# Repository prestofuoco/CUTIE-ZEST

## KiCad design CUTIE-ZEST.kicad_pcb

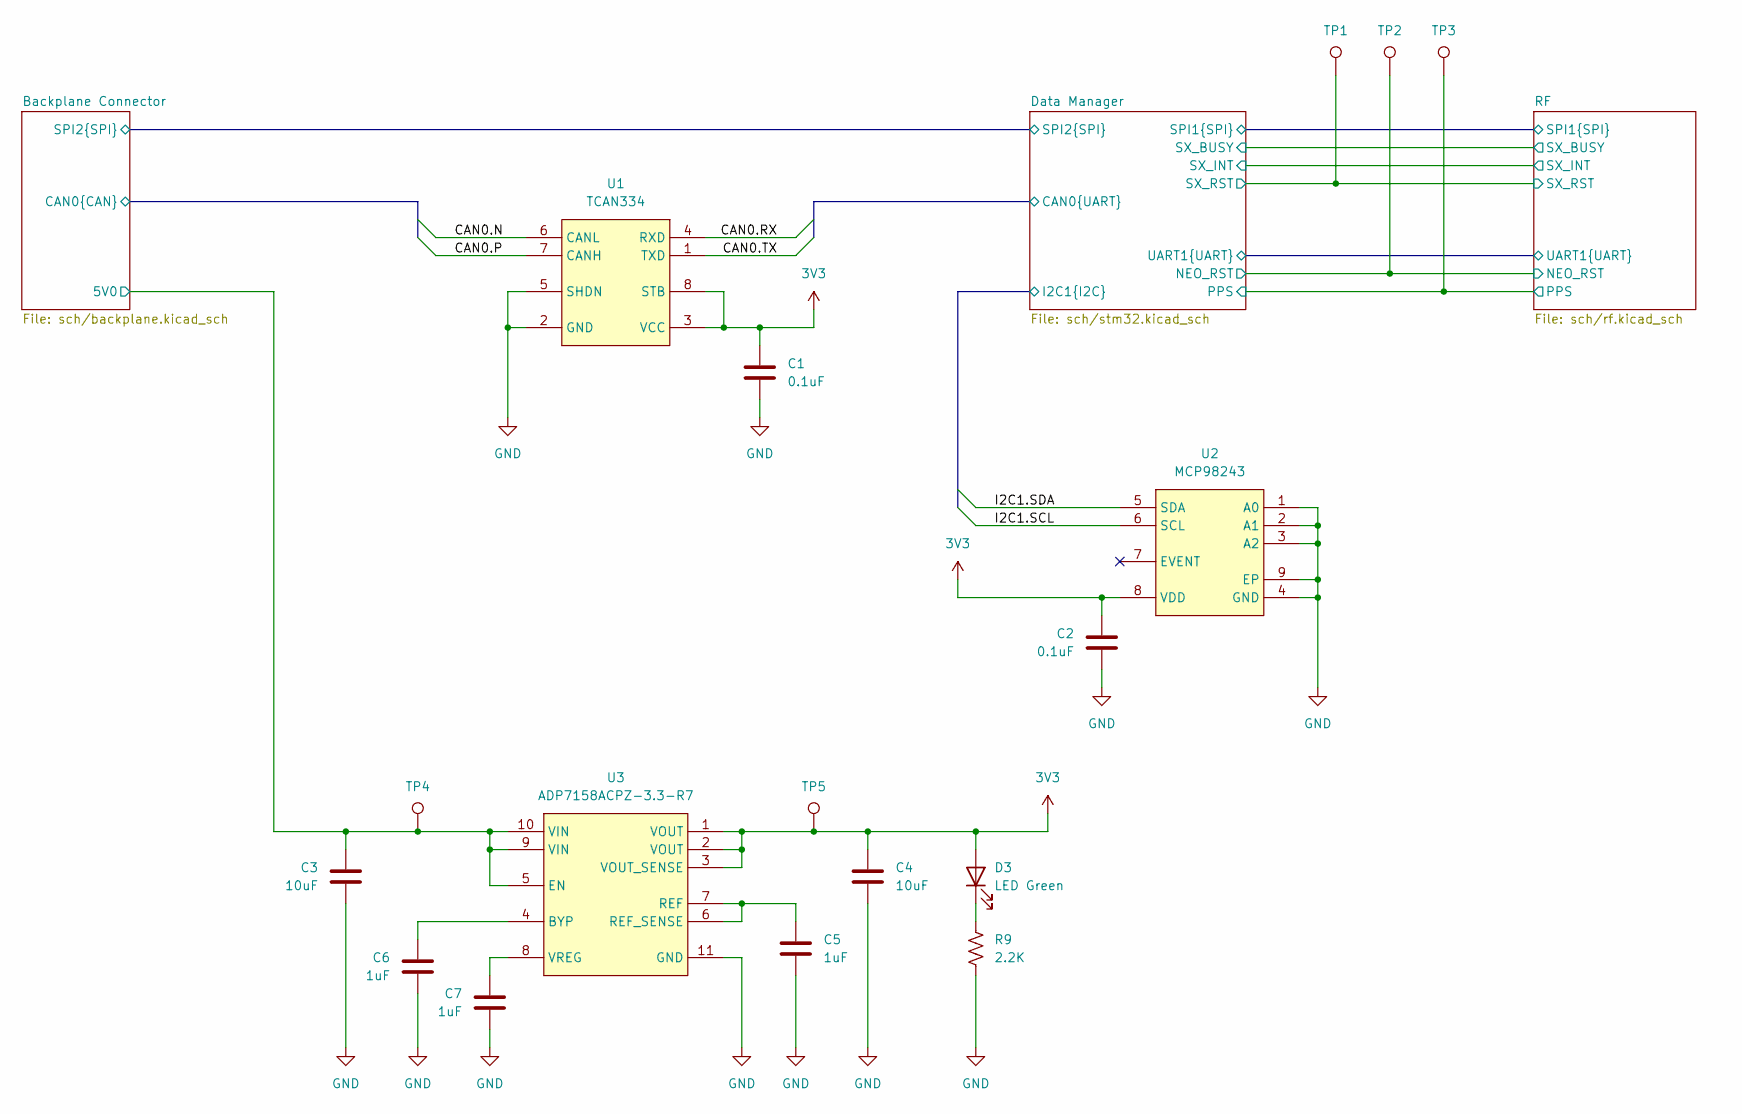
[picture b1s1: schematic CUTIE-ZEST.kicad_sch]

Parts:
C1, C2: 0.1uF; C_0402_1005Metric
C3, C4: 10uF; C_0603_1608Metric
C5, C6, C7: 1uF; C_0603_1608Metric
D3: LED Green; LED_0805_2012Metric
R9: 2.2K; R_0402_1005Metric
TP1, TP2, TP3, TP4, TP5: TestPoint; TestPoint_Pad_D1.0mm
U1: TCAN334; JEITA_SOIC-8_3.9x4.9mm_P1.27mm
U2: MCP98243; DFN-8-1EP_3x2mm_P0.5mm_EP1.3x1.5mm
U3: ADP7158ACPZ-3.3-R7; CP-10-9_ADI

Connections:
3V3: C1.1, C2.1, C4.1, D3.2 (A), TP5.1 (1_1), U1.3 (VCC), U1.8 (STB), U2.8 (VDD), U3.1 (VOUT), U3.2 (VOUT), U3.3 (VOUT_SENSE); also elsewhere on the board
/Backplane Connector/5V0: C3.1, TP4.1 (1_1), U3.5 (EN), U3.9 (VIN), U3.10 (VIN); also elsewhere on the board
/Backplane Connector/CAN0.N: U1.6 (CANL); also elsewhere on the board
/Backplane Connector/CAN0.P: U1.7 (CANH); also elsewhere on the board
/Data Manager/CAN0.RX: U1.4 (RXD); also elsewhere on the board
/Data Manager/CAN0.TX: U1.1 (TXD); also elsewhere on the board
/Data Manager/I2C1.SCL: U2.6 (SCL); also elsewhere on the board
/Data Manager/I2C1.SDA: U2.5 (SDA); also elsewhere on the board
/Data Manager/NEO_RST: TP2.1 (1_1); also elsewhere on the board
/Data Manager/PPS: TP3.1 (1_1); also elsewhere on the board
/Data Manager/SX_RST: TP1.1 (1_1); also elsewhere on the board
GND: C1.2, C2.2, C3.2, C4.2, C5.2, C6.2, C7.2, R9.2, U1.2 (GND), U1.5 (SHDN), U2.1 (A0), U2.2 (A1), U2.3 (A2), U2.4 (GND), U2.9 (EP), U3.11 (GND); also elsewhere on the board
unnamed: D3.1 (K), R9.1
unnamed: C6.1, U3.4 (BYP)
unnamed: C5.1, U3.6 (REF_SENSE), U3.7 (REF)
unnamed: C7.1, U3.8 (VREG)

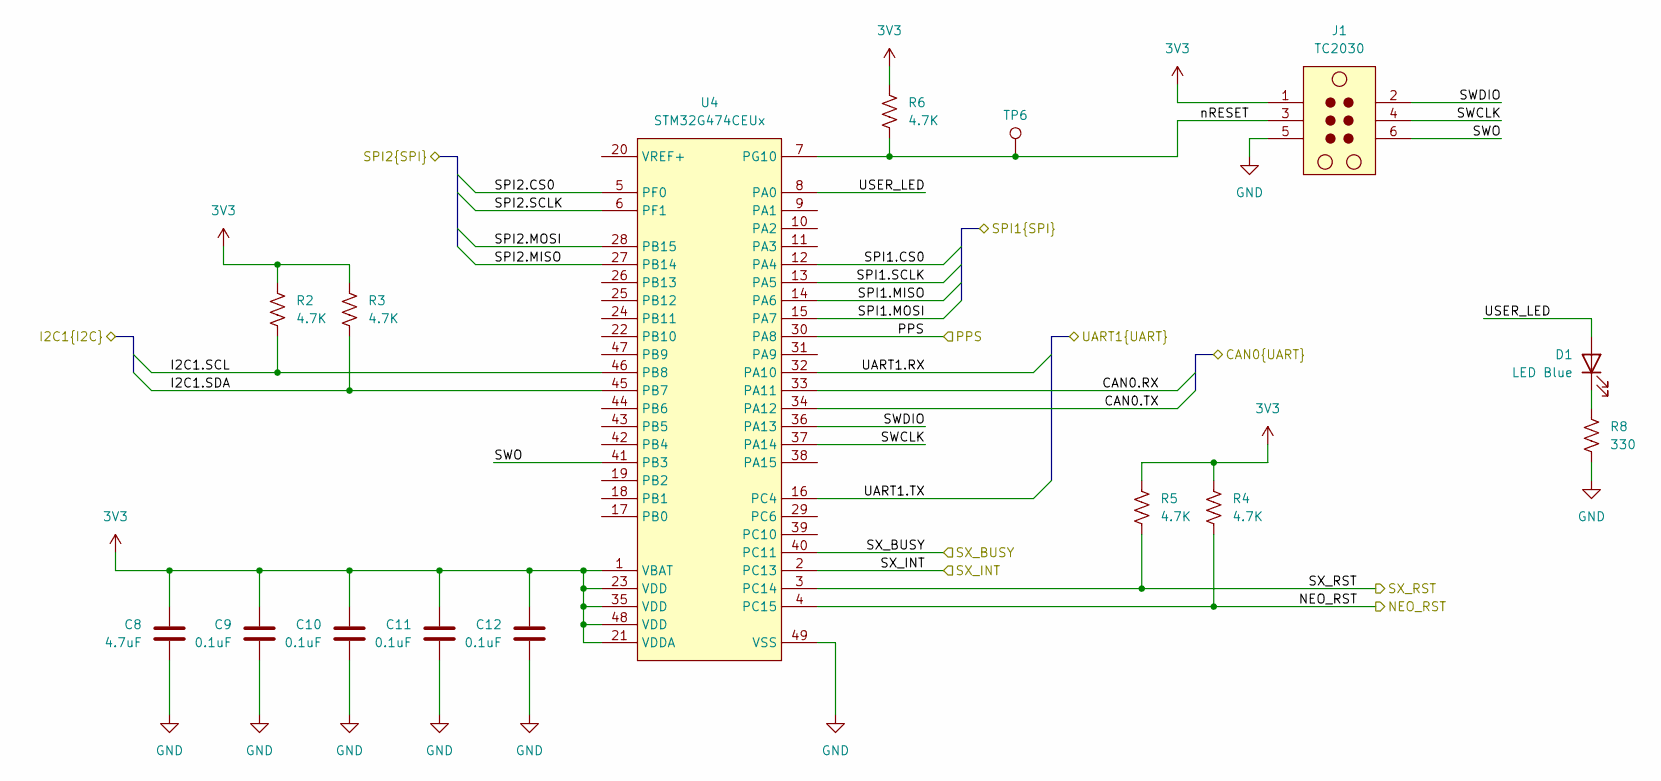
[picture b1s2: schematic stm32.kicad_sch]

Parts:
C8: 4.7uF; C_0603_1608Metric
C9, C10, C11, C12: 0.1uF; C_0402_1005Metric
D1: LED Blue; LED_0805_2012Metric
J1: TC2030; Tag-Connect_TC2030-IDC-NL_2x03_P1.27mm_Vertical
R2, R3, R4, R5, R6: 4.7K; R_0402_1005Metric
R8: 330; R_0402_1005Metric
TP6: TestPoint; TestPoint_Pad_D1.0mm
U4: STM32G474CEUx; QFN-48-1EP_7x7mm_P0.5mm_EP5.6x5.6mm

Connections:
3V3: C8.1, C9.1, C10.1, C11.1, C12.1, J1.1, R2.1, R3.1, R4.1, R5.1, R6.1, U4.1 (VBAT), U4.21 (VDDA), U4.23 (VDD), U4.35 (VDD), U4.48 (VDD); also elsewhere on the board
/Backplane Connector/SPI2.CS0: U4.5 (PF0); also elsewhere on the board
/Backplane Connector/SPI2.MISO: U4.27 (PB14); also elsewhere on the board
/Backplane Connector/SPI2.MOSI: U4.28 (PB15); also elsewhere on the board
/Backplane Connector/SPI2.SCLK: U4.6 (PF1); also elsewhere on the board
/Data Manager/CAN0.RX: U4.33 (PA11); also elsewhere on the board
/Data Manager/CAN0.TX: U4.34 (PA12); also elsewhere on the board
/Data Manager/I2C1.SCL: R2.2, U4.46 (PB8); also elsewhere on the board
/Data Manager/I2C1.SDA: R3.2, U4.45 (PB7); also elsewhere on the board
/Data Manager/NEO_RST: R4.2, U4.4 (PC15); also elsewhere on the board
/Data Manager/PPS: U4.30 (PA8); also elsewhere on the board
/Data Manager/SPI1.CS0: U4.12 (PA4); also elsewhere on the board
/Data Manager/SPI1.MISO: U4.14 (PA6); also elsewhere on the board
/Data Manager/SPI1.MOSI: U4.15 (PA7); also elsewhere on the board
/Data Manager/SPI1.SCLK: U4.13 (PA5); also elsewhere on the board
/Data Manager/SWCLK: J1.4, U4.37 (PA14)
/Data Manager/SWDIO: J1.2, U4.36 (PA13)
/Data Manager/SWO: J1.6, U4.41 (PB3)
/Data Manager/SX_BUSY: U4.40 (PC11); also elsewhere on the board
/Data Manager/SX_INT: U4.2 (PC13); also elsewhere on the board
/Data Manager/SX_RST: R5.2, U4.3 (PC14); also elsewhere on the board
/Data Manager/UART1.RX: U4.32 (PA10); also elsewhere on the board
/Data Manager/UART1.TX: U4.16 (PC4); also elsewhere on the board
/Data Manager/USER_LED: D1.2 (A), U4.8 (PA0)
/Data Manager/nRESET: J1.3, R6.2, TP6.1 (1_1), U4.7 (PG10)
GND: C8.2, C9.2, C10.2, C11.2, C12.2, J1.5, R8.2, U4.49 (VSS); also elsewhere on the board
unnamed: D1.1 (K), R8.1

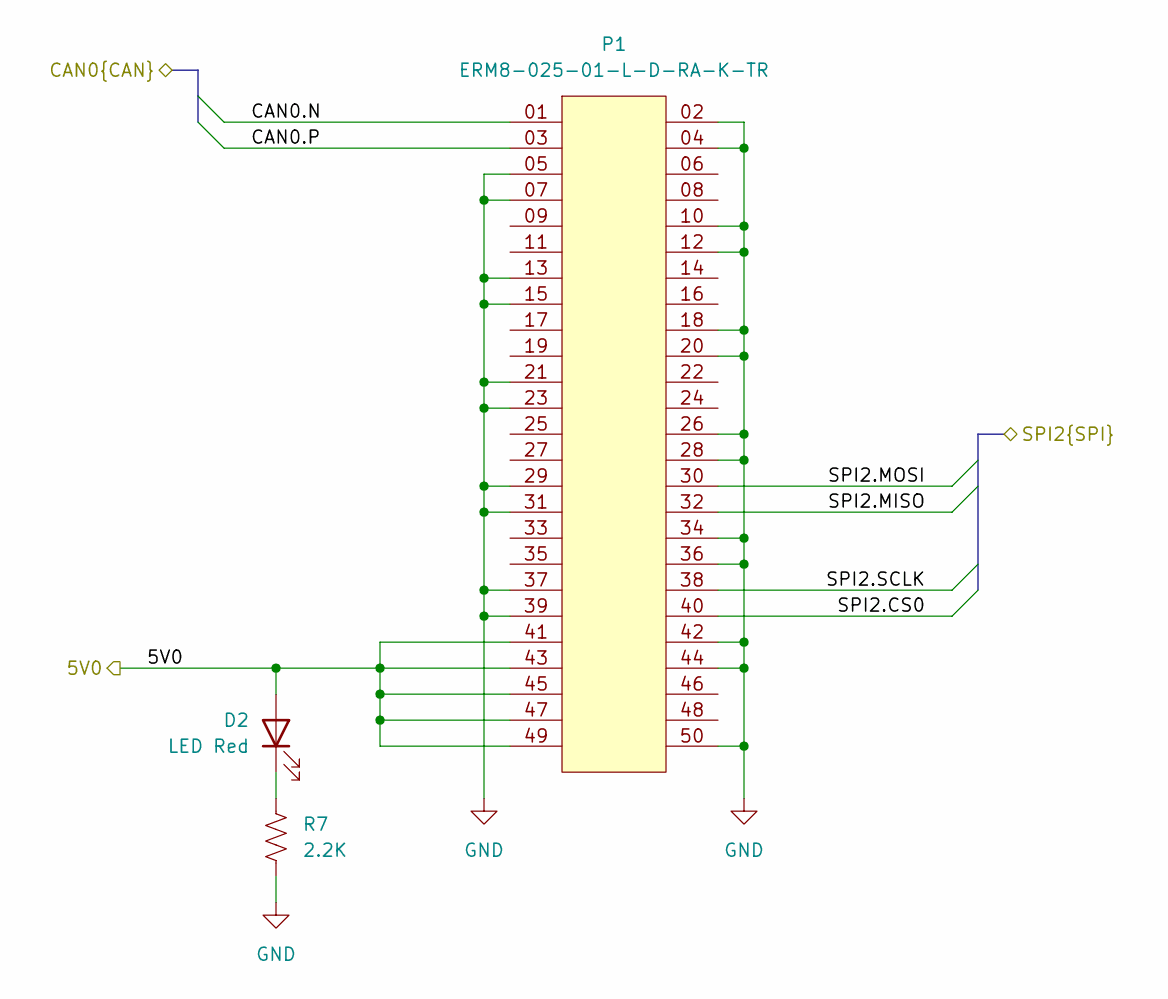
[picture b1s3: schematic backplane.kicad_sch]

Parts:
D2: LED Red; LED_0805_2012Metric
P1: ERM8-025-01-L-D-RA-K-TR; SAMTEC_ERM8-025-XX-X-D-RA-XX
R7: 2.2K; R_0402_1005Metric

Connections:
/Backplane Connector/5V0: D2.2 (A), P1.41, P1.43, P1.45, P1.47, P1.49; also elsewhere on the board
/Backplane Connector/CAN0.N: P1.01; also elsewhere on the board
/Backplane Connector/CAN0.P: P1.03; also elsewhere on the board
/Backplane Connector/SPI2.CS0: P1.40; also elsewhere on the board
/Backplane Connector/SPI2.MISO: P1.32; also elsewhere on the board
/Backplane Connector/SPI2.MOSI: P1.30; also elsewhere on the board
/Backplane Connector/SPI2.SCLK: P1.38; also elsewhere on the board
GND: P1.02, P1.04, P1.05, P1.07, P1.10, P1.12, P1.13, P1.15, P1.18, P1.20, P1.21, P1.23, P1.26, P1.28, P1.29, P1.31, P1.34, P1.36, P1.37, P1.39, P1.42, P1.44, P1.50, R7.2; also elsewhere on the board
unnamed: D2.1 (K), R7.1

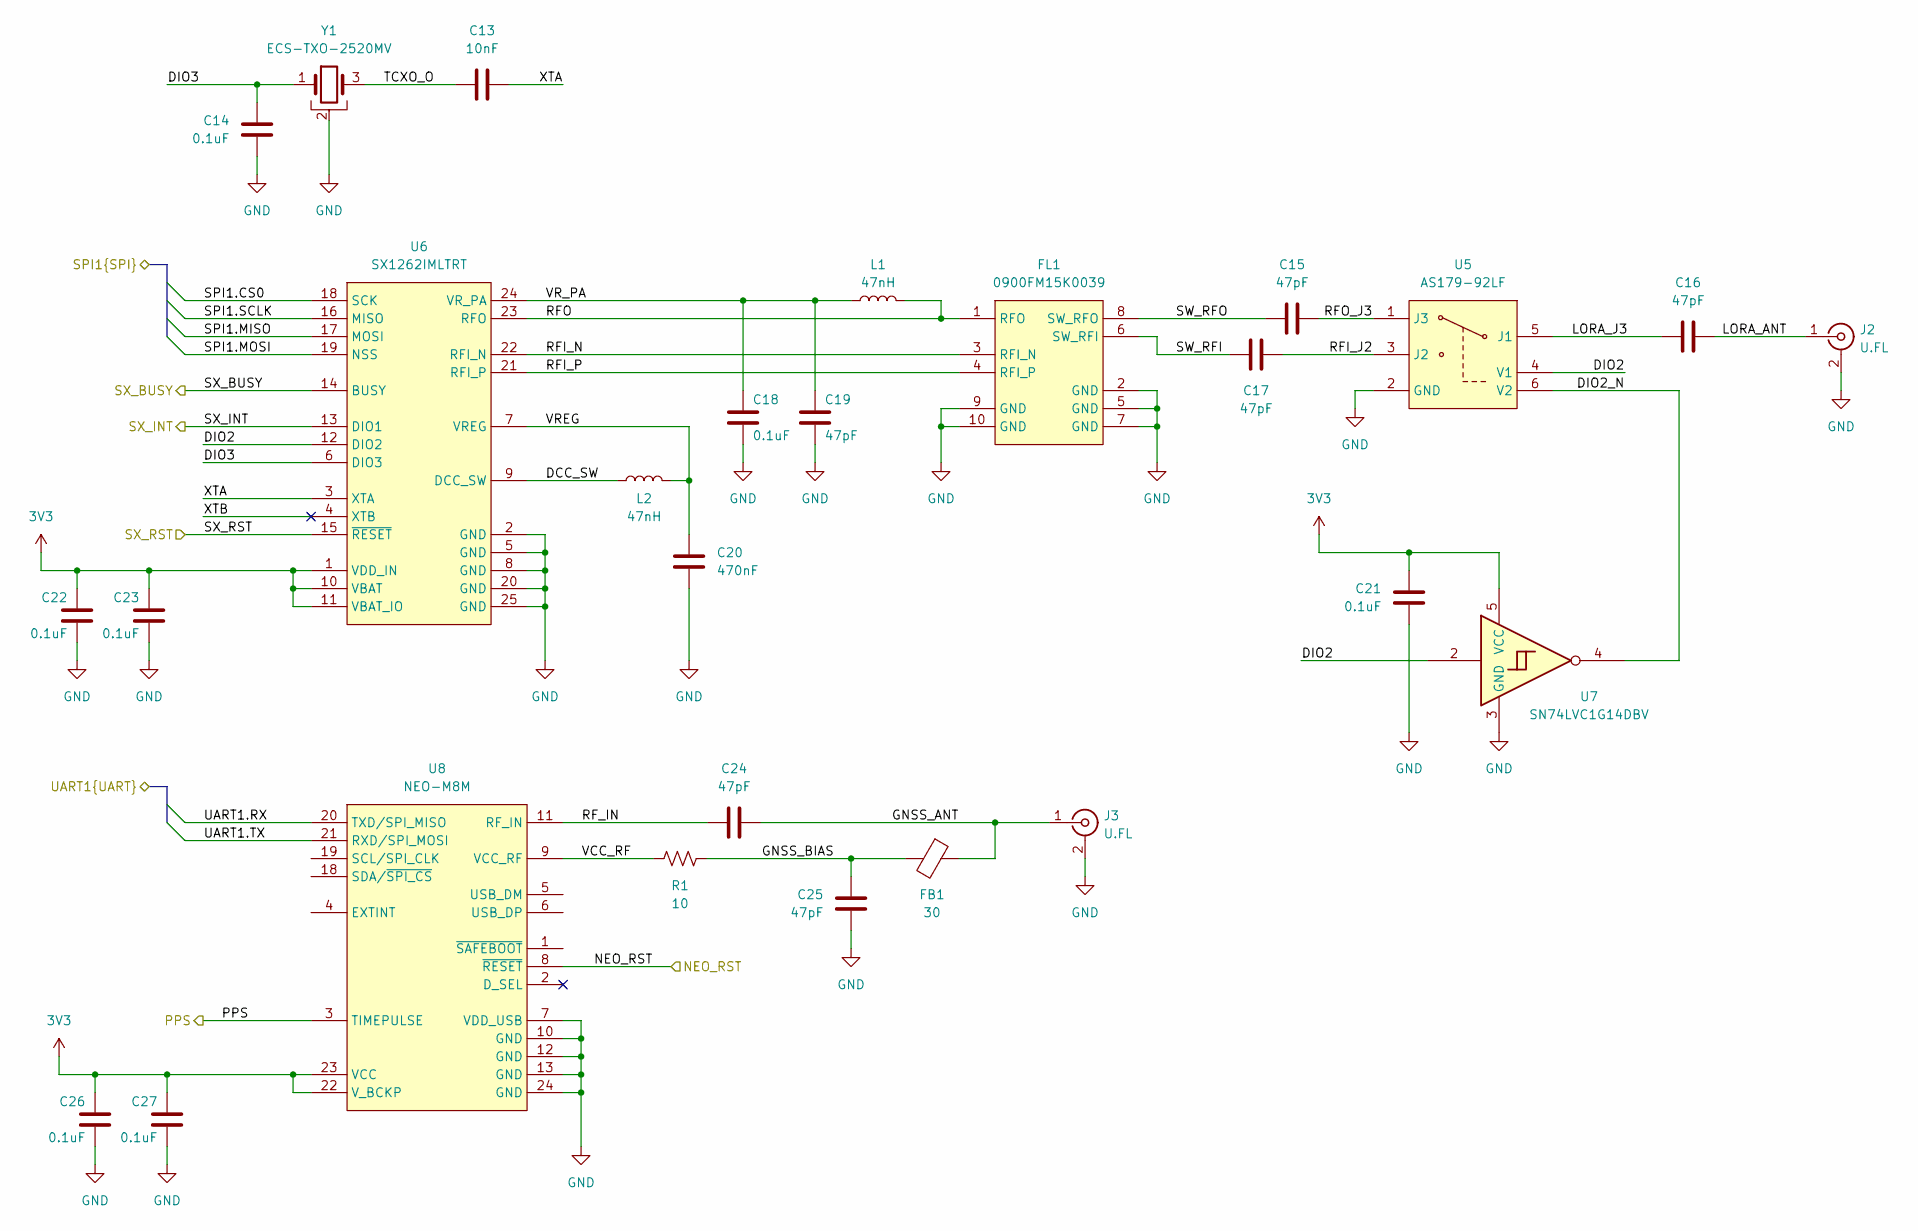
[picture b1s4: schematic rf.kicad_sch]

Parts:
C13: 10nF; C_0402_1005Metric
C14, C18, C21, C22, C23, C26, C27: 0.1uF; C_0402_1005Metric
C15, C16, C17, C19, C24, C25: 47pF; C_0402_1005Metric
C20: 470nF; C_0402_1005Metric
FB1: 30; L_0805_2012Metric
FL1: 0900FM15K0039; Balun_Johanson_0900FM15K0039
J2, J3: U.FL; U.FL_Hirose_U.FL-R-SMT-1_Vertical
L1, L2: 47nH; L_0402_1005Metric
R1: 10; R_0402_1005Metric
U5: AS179-92LF; SOT-363_SC-70-6
U6: SX1262IMLTRT; QFN-24-1EP_4x4mm_P0.5mm_EP2.6x2.6mm
U7: SN74LVC1G14DBV; SOT-23-5
U8: NEO-M8M; ublox_NEO
Y1: ECS-TXO-2520MV; Crystal_SMD_2520-4Pin_2.5x2.0mm

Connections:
3V3: C21.1, C22.1, C23.1, C26.1, C27.1, U6.1 (VDD_IN), U6.10 (VBAT), U6.11 (VBAT_IO), U7.5 (VCC), U8.22 (V_BCKP), U8.23 (VCC); also elsewhere on the board
/Data Manager/NEO_RST: U8.8 (~RESET); also elsewhere on the board
/Data Manager/PPS: U8.3 (TIMEPULSE); also elsewhere on the board
/Data Manager/SPI1.CS0: U6.18 (SCK); also elsewhere on the board
/Data Manager/SPI1.MISO: U6.17 (MOSI); also elsewhere on the board
/Data Manager/SPI1.MOSI: U6.19 (NSS); also elsewhere on the board
/Data Manager/SPI1.SCLK: U6.16 (MISO); also elsewhere on the board
/Data Manager/SX_BUSY: U6.14 (BUSY); also elsewhere on the board
/Data Manager/SX_INT: U6.13 (DIO1); also elsewhere on the board
/Data Manager/SX_RST: U6.15 (~RESET); also elsewhere on the board
/Data Manager/UART1.RX: U8.20 (TXD/SPI_MISO); also elsewhere on the board
/Data Manager/UART1.TX: U8.21 (RXD/SPI_MOSI); also elsewhere on the board
/RF/DCC_SW: L2.1, U6.9 (DCC_SW)
/RF/DIO2: U5.4 (V1), U6.12 (DIO2), U7.2
/RF/DIO2_N: U5.6 (V2), U7.4
/RF/DIO3: C14.1, U6.6 (DIO3), Y1.1, Y1.4
/RF/GNSS_ANT: C24.2, FB1.1, J3.1 (In)
/RF/GNSS_BIAS: C25.1, FB1.2, R1.2
/RF/LORA_ANT: C16.2, J2.1 (In)
/RF/LORA_J3: C16.1, U5.5 (J1)
/RF/RFI_J2: C17.2, U5.3 (J2)
/RF/RFI_N: FL1.3 (RFI_N), U6.22 (RFI_N)
/RF/RFI_P: FL1.4 (RFI_P), U6.21 (RFI_P)
/RF/RFO: FL1.1 (RFO), L1.2, U6.23 (RFO)
/RF/RFO_J3: C15.2, U5.1 (J3)
/RF/RF_IN: C24.1, U8.11 (RF_IN)
/RF/SW_RFI: C17.1, FL1.6 (SW_RFI)
/RF/SW_RFO: C15.1, FL1.8 (SW_RFO)
/RF/TCXO_O: C13.1, Y1.3
/RF/VCC_RF: R1.1, U8.9 (VCC_RF)
/RF/VREG: C20.1, L2.2, U6.7 (VREG)
/RF/VR_PA: C18.1, C19.1, L1.1, U6.24 (VR_PA)
/RF/XTA: C13.2, U6.3 (XTA)
/RF/XTB: U6.4 (XTB)
GND: C14.2, C18.2, C19.2, C20.2, C21.2, C22.2, C23.2, C25.2, C26.2, C27.2, FL1.2 (GND), FL1.5 (GND), FL1.7 (GND), FL1.9 (GND), FL1.10 (GND), J2.2 (Ext), J3.2 (Ext), U5.2 (GND), U6.2 (GND), U6.5 (GND), U6.8 (GND), U6.20 (GND), U6.25 (GND), U7.3 (GND), U8.7 (VDD_USB), U8.10 (GND), U8.12 (GND), U8.13 (GND), U8.24 (GND), Y1.2; also elsewhere on the board

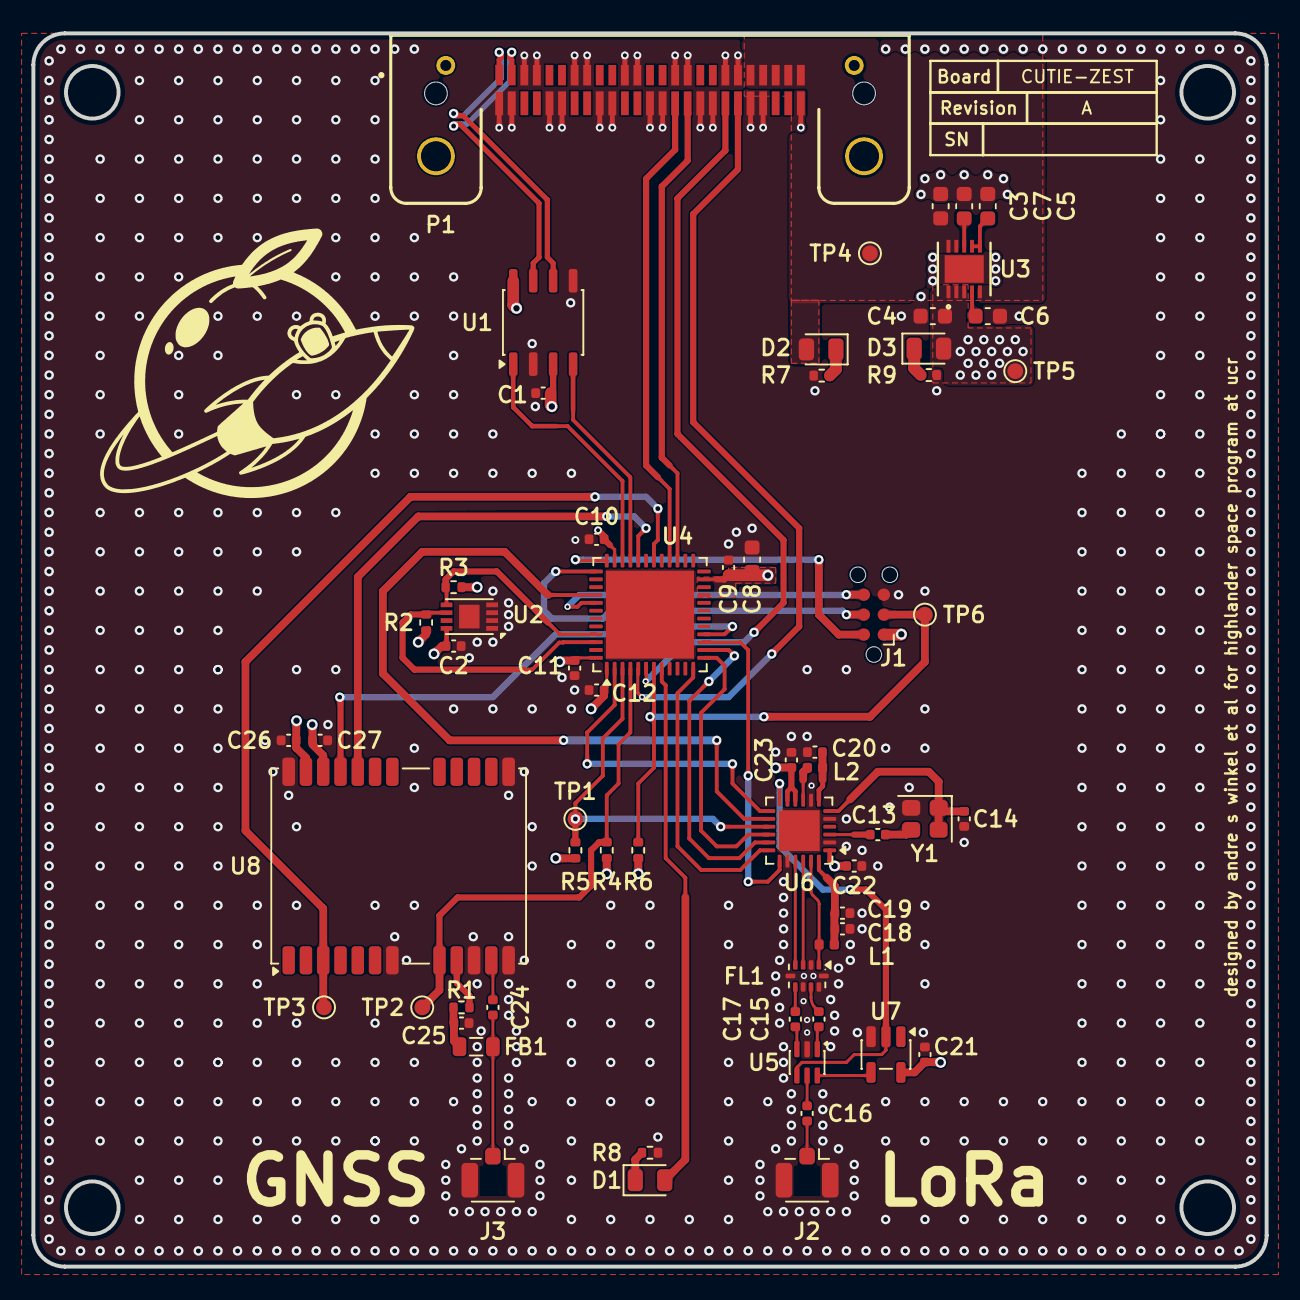
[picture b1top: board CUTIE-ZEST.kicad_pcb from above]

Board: 4 copper layers, 78.5 x 78.5 mm, 62 parts (0 on the bottom side), 56 nets.

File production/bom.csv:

Designator,Footprint,Quantity,Value,LCSC Part #
"C1, C10, C11, C12, C14, C18, C2, C21, C22, C23, C26, C27, C9",0402,13,0.1uF,
C13,0402,1,10nF,
"C15, C16, C17, C19, C24, C25",0402,6,47pF,
C20,0402,1,470nF,
"C3, C4",0603,2,10uF,
"C5, C6, C7",0603,3,1uF,
C8,0603,1,4.7uF,
D1,0805,1,LED Blue,
D2,0805,1,LED Red,
D3,0805,1,LED Green,
FB1,0805,1,30,
FL1,Balun_Johanson_0900FM15K0039,1,0900FM15K0039,
"J2, J3",U.FL_Hirose_U.FL-R-SMT-1_Vertical,2,U.FL,
"L1, L2",0402,2,47nH,
P1,SAMTEC_ERM8-025-XX-X-D-RA-XX,1,ERM8-025-01-L-D-RA-K-TR,
R1,0402,1,10,
"R2, R3, R4, R5, R6",0402,5,4.7K,
"R7, R9",0402,2,2.2K,
R8,0402,1,330,
"TP1, TP2, TP3, TP4, TP5, TP6",TestPoint_Pad_D1.0mm,6,TestPoint,
U1,JEITA_SOIC-8_3.9x4.9mm_P1.27mm,1,TCAN334,
U2,DFN-8-1EP_3x2mm_P0.5mm_EP1.3x1.5mm,1,MCP98243,
U3,CP-10-9_ADI,1,ADP7158ACPZ-3.3-R7,
U4,QFN-48-1EP_7x7mm_P0.5mm_EP5.6x5.6mm,1,STM32G474CEUx,
U5,SOT-363_SC-70-6,1,AS179-92LF,
U6,QFN-24-1EP_4x4mm_P0.5mm_EP2.6x2.6mm,1,SX1262IMLTRT,
U7,SOT-23-5,1,SN74LVC1G14DBV,
U8,ublox_NEO,1,NEO-M8M,
Y1,Crystal_SMD_2520-4Pin_2.5x2.0mm,1,ECS-TXO-2520MV,

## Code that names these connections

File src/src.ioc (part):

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Mcu.Name=STM32G473C(B-C-E)Ux
Mcu.Package=UFQFPN48
Mcu.UserName=STM32G473CEUx
PA0.GPIOParameters=GPIO_Label
PA0.GPIO_Label=USER_LED
PA0.Signal=GPIO_Output
PA10.Mode=Asynchronous
PA10.Signal=USART1_RX
PA11.Mode=FDCAN_Activate
PA11.Signal=FDCAN1_RX
PA12.Mode=FDCAN_Activate
PA12.Signal=FDCAN1_TX
PA13.Mode=Trace_Asynchronous_SW
PA13.Signal=SYS_JTMS-SWDIO
PA14.Mode=Trace_Asynchronous_SW
PA14.Signal=SYS_JTCK-SWCLK
PA4.GPIOParameters=GPIO_Speed,GPIO_Label
PA4.GPIO_Label=SPI1_CS0
PA4.GPIO_Speed=GPIO_SPEED_FREQ_VERY_HIGH
PA4.Signal=GPIO_Output
PA5.Mode=Full_Duplex_Master
PA5.Signal=SPI1_SCK
PA6.Mode=Full_Duplex_Master
PA6.Signal=SPI1_MISO
PA7.Mode=Full_Duplex_Master
PA7.Signal=SPI1_MOSI
PA8.GPIOParameters=GPIO_Label
PA8.GPIO_Label=PPS
PA8.Signal=GPIO_Input
PB14.Mode=Full_Duplex_Master
PB14.Signal=SPI2_MISO
PB15.Mode=Full_Duplex_Master
PB15.Signal=SPI2_MOSI
PB3.Mode=Trace_Asynchronous_SW
PB3.Signal=SYS_JTDO-SWO
PB7.Mode=I2C
PB7.Signal=I2C1_SDA
PB8-BOOT0.Mode=I2C
PB8-BOOT0.Signal=I2C1_SCL
PC11.GPIOParameters=GPIO_Label
PC11.GPIO_Label=SX_BUSY
PC11.Signal=GPIO_Input
PC13.GPIOParameters=GPIO_Label
PC13.GPIO_Label=SX_INT
PC13.Signal=GPIO_Input
PC14-OSC32_IN.GPIOParameters=GPIO_Label
PC14-OSC32_IN.GPIO_Label=SX_RST
PC14-OSC32_IN.Signal=GPIO_Output
PC15-OSC32_OUT.GPIOParameters=GPIO_Label
PC15-OSC32_OUT.GPIO_Label=NEO_RST
PC15-OSC32_OUT.Signal=GPIO_Output
PC4.Mode=Asynchronous
PC4.Signal=USART1_TX
PF0-OSC_IN.GPIOParameters=GPIO_Speed,GPIO_Label
PF0-OSC_IN.GPIO_Label=SPI2_CS0
PF0-OSC_IN.GPIO_Speed=GPIO_SPEED_FREQ_VERY_HIGH
PF0-OSC_IN.Signal=GPIO_Output
PF1-OSC_OUT.Mode=Full_Duplex_Master
PF1-OSC_OUT.Signal=SPI2_SCK
PG10-NRST.GPIOParameters=GPIO_Label
PG10-NRST.GPIO_Label=NRST
PG10-NRST.Signal=GPIO_Input
RCC.HSE_VALUE=8000000
RCC.SYSCLKFreq_VALUE=16000000
board=custom

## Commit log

2026-03-31 update for prod
2026-04-01 bom for assembly
2026-04-08 push for fab
2026-04-10 initialized firmware structure
2026-04-13 added pdf
2026-04-14 added driver code for sx126x, minmea
2026-04-25 gps driver receive & processing buffers
2026-04-30 quick push, add time to struct
2026-04-30 LED Blinking function for connection
2026-05-09 amend small changes to gps_driver.c finalizing structure before shifting development focus to lora
2026-05-13 Lora_driver.h and Lora_driver.c
    Updated main and lora drivers.
2026-05-15 Updated changes to Lora Driver
2026-05-18 Changes in lora_driver according to pull request
